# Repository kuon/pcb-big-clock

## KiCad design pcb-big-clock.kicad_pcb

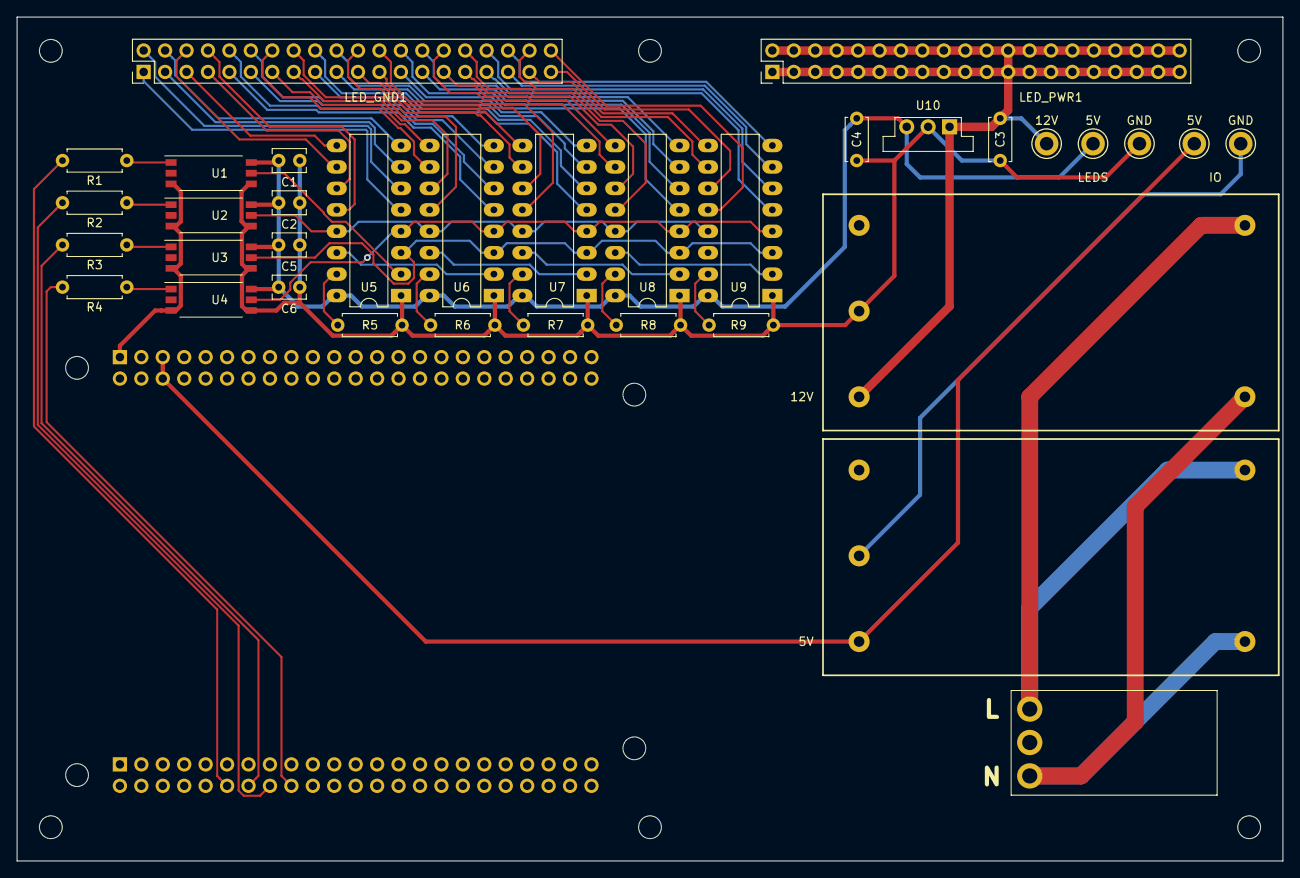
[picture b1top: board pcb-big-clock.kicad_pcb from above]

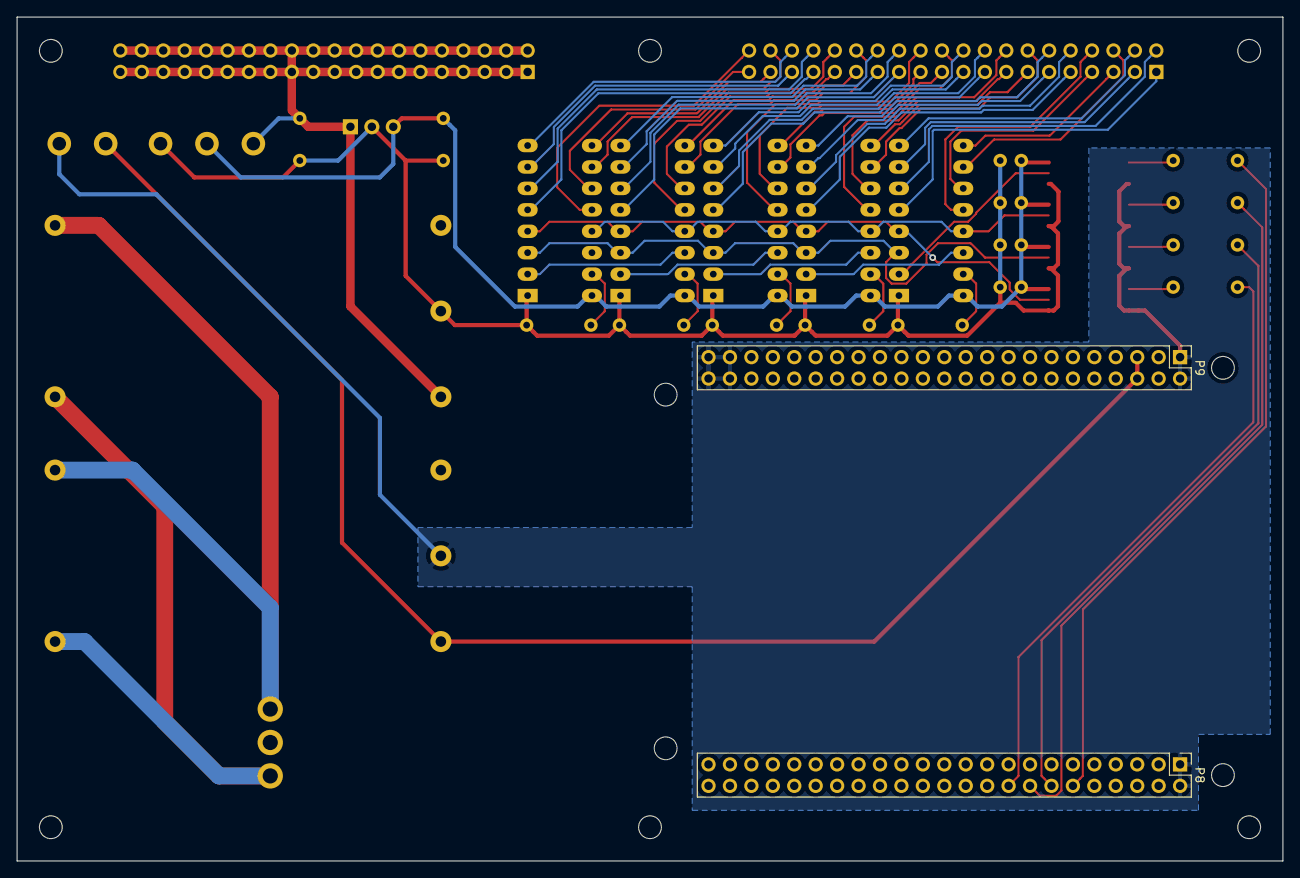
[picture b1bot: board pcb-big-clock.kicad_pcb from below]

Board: 2 copper layers, 150.0 x 100.0 mm, 37 parts (2 on the bottom side), 68 nets.

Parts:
5V, 5V#2, 12V: TestPoint; TestPoint_Keystone_5005-5009_Compact
C1, C2, C5, C6: 100n; C_Disc_D3.8mm_W2.6mm_P2.50mm
C3, C4: 10u; C_Disc_D5.0mm_W2.5mm_P5.00mm
GND: TestPoint; TestPoint_Keystone_5005-5009_Compact
GND#2: TestPoint; TestPoint_Keystone_5005-5009_Compact
JAC1: Conn_01x03_Male; KK header right angle 3.96mm 1x3
LED_GND1: Conn_02x20_Counter_Clockwise; PinHeader_2x20_P2.54mm_Vertical
LED_PWR1: Conn_02x20_Counter_Clockwise; PinHeader_2x20_P2.54mm_Vertical
P1, P2: RAC10-KS; RAC10-K
P8, P9: Conn_02x23_Odd_Even; PinHeader_2x23_P2.54mm_Vertical
R1, R2, R3, R4: 470R; R_Axial_DIN0207_L6.3mm_D2.5mm_P7.62mm_Horizontal
R5, R6, R7, R8, R9: 1K; R_Axial_DIN0207_L6.3mm_D2.5mm_P7.62mm_Horizontal
U1, U2, U3, U4: TLP2767; SO-6L_10x3.84mm_P1.27mm
U5, U6, U7, U8, U9: TLC5916IN; DIP-16_W7.62mm_LongPads
U10: OKI-78SR-5_1.5-W36-C; Converter_DCDC_muRata_OKI-78SR_Vertical

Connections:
+5V: 5V.1, C1.2, C2.2, C4.1, C5.2, C6.2, U1.6, U2.6, U3.6, U4.6, U5.16, U6.16, U7.16, U8.16, U9.16, U10.3
+12V: 12V.1, C3.1, LED_PWR1.1, LED_PWR1.2, LED_PWR1.3, LED_PWR1.4, LED_PWR1.5, LED_PWR1.6, LED_PWR1.7, LED_PWR1.8, LED_PWR1.9, LED_PWR1.10, LED_PWR1.11, LED_PWR1.12, LED_PWR1.13, LED_PWR1.14, LED_PWR1.15, LED_PWR1.16, LED_PWR1.17, LED_PWR1.18, LED_PWR1.19, LED_PWR1.20, LED_PWR1.21, LED_PWR1.22, LED_PWR1.23, LED_PWR1.24, LED_PWR1.25, LED_PWR1.26, LED_PWR1.27, LED_PWR1.28, LED_PWR1.29, LED_PWR1.30, LED_PWR1.31, LED_PWR1.32, LED_PWR1.33, LED_PWR1.34, LED_PWR1.35, LED_PWR1.36, LED_PWR1.37, LED_PWR1.38, LED_PWR1.39, LED_PWR1.40, P1.5, U10.1
/BB_CLK: P8.14, R3.2
/BB_LE: P8.18, R4.2
/BB_SDI: P8.12, R1.2
/CLK: U3.5, U5.3, U6.3, U7.3, U8.3, U9.3
/IO_5V: 5V#2.1, P2.5, P9.5, P9.6
/IO_GND: GND#2.1, P2.4, P8.1, P8.2, P9.1, P9.2, P9.43, P9.44, P9.45, P9.46, U1.3, U2.3, U3.3, U4.3
/LE: U4.5, U5.4, U6.4, U7.4, U8.4, U9.4
/SDI: U1.5, U5.2
/~BB_OE~: P8.16, R2.2
/~OE~: U2.5, U5.13, U6.13, U7.13, U8.13, U9.13
GND: C1.1, C2.1, C3.2, C4.2, C5.1, C6.1, GND.1, P1.4, R5.2, R6.2, R7.2, R8.2, R9.2, U1.4, U2.4, U3.4, U4.4, U5.1, U6.1, U7.1, U8.1, U9.1, U10.2
unnamed: JAC1.1, P1.2, P2.2
unnamed: JAC1.3, P1.1, P2.1
unnamed: LED_GND1.1, U5.5
unnamed: LED_GND1.2, U5.6
unnamed: LED_GND1.3, U5.7
unnamed: LED_GND1.4, U5.8
unnamed: LED_GND1.5, U5.9
unnamed: LED_GND1.6, U5.10
unnamed: LED_GND1.7, U5.11
unnamed: LED_GND1.8, U5.12
unnamed: LED_GND1.9, U6.5
unnamed: LED_GND1.10, U6.6
unnamed: LED_GND1.11, U6.7
unnamed: LED_GND1.12, U6.8
unnamed: LED_GND1.13, U6.9
unnamed: LED_GND1.14, U6.10
unnamed: LED_GND1.15, U6.11
unnamed: LED_GND1.16, U6.12
unnamed: LED_GND1.17, U7.5
unnamed: LED_GND1.18, U7.6
unnamed: LED_GND1.19, U7.7
unnamed: LED_GND1.20, U7.8
unnamed: LED_GND1.21, U7.9
unnamed: LED_GND1.22, U7.10
unnamed: LED_GND1.23, U7.11
unnamed: LED_GND1.24, U7.12
unnamed: LED_GND1.25, U8.5
unnamed: LED_GND1.26, U8.6
unnamed: LED_GND1.27, U8.7
unnamed: LED_GND1.28, U8.8
unnamed: LED_GND1.29, U8.9
unnamed: LED_GND1.30, U8.10
unnamed: LED_GND1.31, U8.11
unnamed: LED_GND1.32, U8.12
unnamed: LED_GND1.33, U9.5
unnamed: LED_GND1.34, U9.6
unnamed: LED_GND1.35, U9.7
unnamed: LED_GND1.36, U9.8
unnamed: LED_GND1.37, U9.9
unnamed: LED_GND1.38, U9.10
unnamed: LED_GND1.39, U9.11
unnamed: LED_GND1.40, U9.12
unnamed: R1.1, U1.1
unnamed: R2.1, U2.1
unnamed: R3.1, U3.1
unnamed: R4.1, U4.1
unnamed: R5.1, U5.15
unnamed: R6.1, U6.15
unnamed: R7.1, U7.15
unnamed: R8.1, U8.15
unnamed: R9.1, U9.15
unnamed: U5.14, U6.2
unnamed: U6.14, U7.2
unnamed: U7.14, U8.2
unnamed: U8.14, U9.2

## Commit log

2021-11-10 Big clock PCB
